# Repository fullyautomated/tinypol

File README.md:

# 48-V Input Affordable 1.2-A Output Converter / SY8502

## Overview

This design is based around the Silergy SY8502FCC converter.  
[IC Datasheet](/1809231105_Silergy-Corp-SY8502FCC_C87752.pdf). [Board Schematic](/tinypol_color.pdf).  
For layout, see the .kicad_pcb file in the repository.

## Use

Connect the input side to the power source, and the output side to the load. The converter powers on automatically above approx. 6.2V input. Output is programmed to 5.2 volt, can be changed by replacing R3 and/or R4. Reference voltage is 1.2 V. Supported input voltage is around 56-V, above which the D1 TVS diode will start to clamp. You can remove this to increase maximum input voltage to 85V abs max, but then you should avoid hot-plugging the board.

There are two ways to shut down the converter while input power is present. 
 - Either apply a logic high to input labled OFF (J4) *don't exceed +/- 12V on this pin*, or 
 - pull EN input low. The EN pin is pulled up on-board to VIN with 100kOhm, therefore the circuit you use to discharge EN must withstand the maximum VIN you plan to apply.

 Alternatively, you can disconnect the input.

## Properties

|                          Specifications |                                                                    |
|----------------------------------------:|--------------------------------------------------------------------|
|                             Dimensions: | 25x42x6mm (without pin headers)                                    |
|                                   Mass: | 4.8g (without pin headers)                                         |
|                          Mounting Hole: | M3 at (-6;-4)mm from bottom right corner                           |
|                          Input Voltage: | 6.8V - 56V                                                         |
|                         Output Voltage: | 5.2V (default)<br>Optionally between 1.8V and 24V                  |
|             Internal Reference Voltage: | 1.2V                                                               |
|                          Output Ripple: | 500mVpp with no load<br>80mVpp in Continuous Conduction Mode       |
|                         Output Current: | 1.8A peak<br>1.2A continuous                                       |
|                            Power Stage: | Synchronous buck with 500mOhm (HS) and 240mOhm (LS) nMOS switches  |
|             Overtemperature Protection: | Yes, at 150 degrees Celsius                                        |
|               Short Circuit Protection: | Yes, at 2A                                                         |
|              Fixed Switching Frequency: | No. <br>In Continuous Conduction Mode fSW is approx. 340 kHz       |
|                             Soft Start: | 2ms, fixed in silicon                                              |
| Transient Input Overvoltage Protection: | Yes, with on-board TVS diode                                       |
|          Output Overvoltage Protection: | No.                                                                |
|                       Hot-Plug Capable: | Yes.                                                               |
|                          Soft Shutdown: | Yes (logic high on OFF pin) or<br>Yes (pulling EN pin low)         |
|                    Output ON Indicator: | No.                                                                |
|                      Power Good Output: | No.                                                                |
|                                   RoHS: | Yes, plus tantalum-free.                                           |

## Planned Future Changes

 - Add a capacitor at SYE pin to de-glitch.
 - Add an output indicator LED.

## Test report

The IC looks quite OK! Output has little noise (thanks to the plentiful output MLCCs) but high ripple because of low switching frequency and hysteretic operation. Rectifier MOSFET control looks good. Short circuit test looks good. Startup after short is good.

The SYE (enable) pin does not seem to be properly deglitched internally. I can make it behave erronously by feeding noise into EN. The on-board 100k pullup is strong enough to counteract spurious noise, but you can drive it externally to make it do weird things.

I can tickle the IC to make the output oscillate, but it settles rather quickly. Would not use it to power sensitive circuits directly, without a second regulator.

Driving it close to 2 A output makes it run very hot. The thermal pad below the IC seems to be well soldered and the board is sinking the heat. Inductor heats up quite a bit; a better one would probably help increase efficiency, but it is okay for its typical use case, and you would not get much more current out of this anyway. The board has nice thermal mass!

Tried adding 2200uF electrolytic cap to the output, this did not reduce ripple (because it is determined by the hysteresis of the comparator) but pushed the switching frequency down to the audible range with low load. 

One weirdness I observed: when running it with a hard short at its output the output current is initially clamped at 2A, at which the converter heates up, which changes the overcurrent comparator's threshold. After thermal shutdown kicked in, I let the IC cool down, and repeated the test. Now the output current into a short was only 1A. This did not change after power cycling the IC, and seems to be permanent. I will repeat this test on different boards too, but I want to set up a test script first so I can compare chips before-after, and that needs more work on our lab instrumentation.

Either way, this IC looks very usable, while being much cheaper than any of its alternatives.

### Planned Future Tests:
 - Characterize:
   - Iq over Vin with EN=low and EN=high
   - Efficiency curve (needs work on lab equipment)
 - Increasing Cff to optimize load step behavior
 - Adding C to SYE to test glitch improvement

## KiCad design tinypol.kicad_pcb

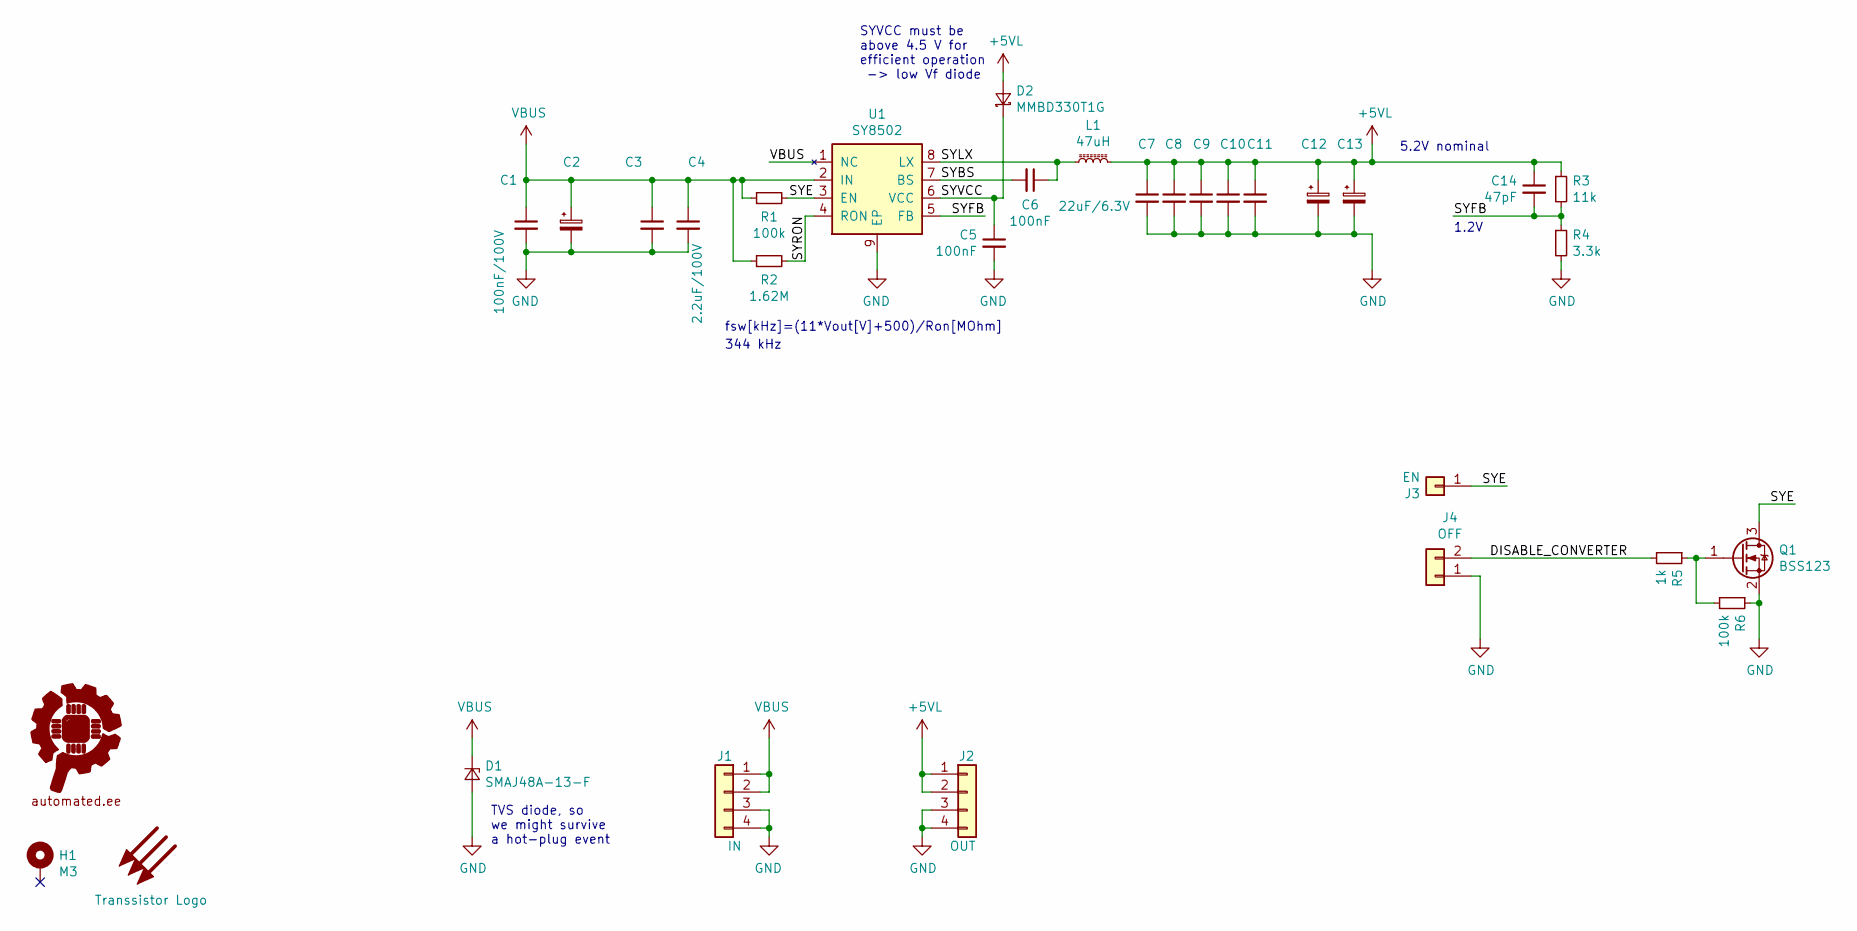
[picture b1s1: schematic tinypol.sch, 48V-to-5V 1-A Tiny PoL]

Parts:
C1: 100nF/100V; C_0603_1608Metric
C2, C12, C13: d.n.p.; C_Elec_6.3x5.8
C3: 2.2uF/100V; C_0805_2012Metric
C4: 2.2uF/100V; C_1210_3225Metric
C5: 100nF; C_0603_1608Metric
C6: 100nF; C_0402_1005Metric
C7, C8, C9: 22uF/6.3V; C_0603_1608Metric
C10: 22uF/6.3V; C_0805_2012Metric
C11: 22uF/6.3V; C_1210_3225Metric
C14: 47pF; C_0603_1608Metric
D1: SMAJ48A-13-F; D_SMA
D2: MMBD330T1G; D_SOT-23_ANK
G1: Fully_Automated_Logo; falogo_small_copper
G2: Transsistor Logo; transistor_10x10mm
H1: M3; MountingHole_3.2mm_M3_ISO7380_Pad
J1: IN; PinHeader_1x04_P2.54mm_Horizontal
J2: OUT; PinHeader_1x04_P2.54mm_Horizontal
J3: EN; PinHeader_1x01_P2.54mm_Horizontal
J4: OFF; PinHeader_1x02_P2.54mm_Horizontal
L1: 47uH; L_Bourns_SRN6045TA
Q1: BSS123; SOT-23
R1, R6: 100k; R_0603_1608Metric
R2: 1.62M; R_0603_1608Metric
R3: 11k; R_0603_1608Metric
R4: 3.3k; R_0603_1608Metric
R5: 1k; R_0603_1608Metric
U1: SY8502; SO8E_Silergy_4x5mm_EP3.4x2.55mm

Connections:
+5VL: C7.1, C8.1, C9.1, C10.1, C11.1, C12.1, C13.1, C14.1, D2.2 (A), J2.1, J2.2, L1.2, R3.1
/DISABLE_CONVERTER: J4.2, R5.2
/SYBS: C6.2, U1.7 (BS)
/SYE: J3.1, Q1.3 (D), R1.2, U1.3 (EN)
/SYFB: C14.2, R3.2, R4.1, U1.5 (FB)
/SYLX: C6.1, L1.1, U1.8 (LX)
/SYRON: R2.2, U1.4 (RON)
/SYVCC: C5.1, D2.1 (K), U1.6 (VCC)
GND: C1.2, C2.2, C3.2, C4.2, C5.2, C7.2, C8.2, C9.2, C10.2, C11.2, C12.2, C13.2, D1.2 (A), J1.3, J1.4, J2.3, J2.4, J4.1, Q1.2 (S), R4.2, R6.1, U1.9 (EP)
unnamed: Q1.1 (G), R5.1, R6.2
VBUS: C1.1, C2.1, C3.1, C4.1, D1.1 (K), J1.1, J1.2, R1.1, R2.1, U1.1 (NC), U1.2 (IN)

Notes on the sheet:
TVS diode, so we might survive a hot-plug event
5.2V nominal
344 kHz
fsw[kHz]=(11*Vout[V]+500)/Ron[MOhm]
1.2V
SYVCC must be above 4.5 V for efficient operation -> low Vf diode

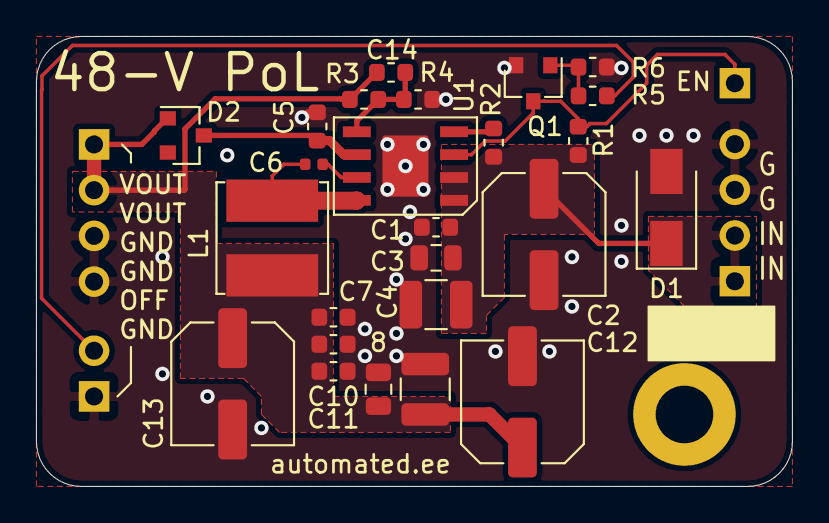
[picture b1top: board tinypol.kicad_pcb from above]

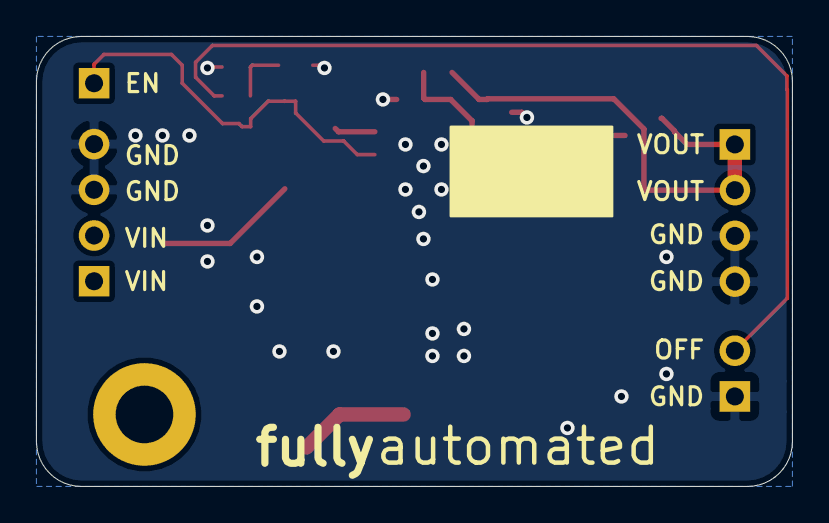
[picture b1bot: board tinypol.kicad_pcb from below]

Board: 2 copper layers, 42.0 x 25.0 mm, 31 parts (3 on the bottom side), 11 nets.

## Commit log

2020-01-03 publish in this org
2020-01-03 added gitignore
